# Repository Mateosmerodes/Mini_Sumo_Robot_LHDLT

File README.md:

# Mini_Sumo_Robot_LHDLT
Repositorio de información y código del proyecto mini-sumo del equipo LHDT (Los Hombres de las Tabernas).

- [`Robot_Mini-Sumo/`](Robot_Mini-Sumo/README.md): diseño actual (v2 básico, 2 motores, placa de agujero pasante).
- [`archivo/v1-4motores/`](archivo/v1-4motores/ARCHIVO.md): todo el diseño anterior (v1, 4 motores), guardado tal cual.

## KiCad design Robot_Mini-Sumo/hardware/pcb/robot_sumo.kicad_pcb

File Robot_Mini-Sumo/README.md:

# 🍺 Robot Mini-Sumo · LHDT (Los Hombres de las Tabernas)

Robot mini-sumo autónomo (10 × 10 cm, < 500 g) para **Tecnología Eléctrica**, Grado en Robótica (USC). Reglamento de referencia: OSHWDem Mini Sumo.

**Equipo:** Mateo Esmerodes Rodríguez · Paulo Bouza García · Mario Costoya Mera

## Diseño actual: v2 básico (23/11/2026)

Robot sencillo para cumplir: **2 motores N20**, **ESP32-S3-DevKitC-1**, **2 sensores de distancia VL53L0X**, **2 sensores de suelo QRE1113**, batería LiPo 2S y el **módulo de arranque ST4RT** del profesor. Placa propia de **agujero pasante**, con los módulos enchufados y todo rotulado en la serigrafía.

Nada está montado ni probado todavía.

| Qué | Dónde |
|---|---|
| Diseño completo: piezas, pines, placa, cálculos, montaje y compra | [docs/01-Diseno-v2-basico.md](docs/01-Diseno-v2-basico.md) |
| Proyecto KiCad (esquemático y PCB) | [hardware/pcb/](hardware/pcb/) |
| Ficheros para pedir la placa (Gerber, BOM, esquema en PDF) | [hardware/pcb/fabricacion/](hardware/pcb/fabricacion/) |
| Chasis (script de Fusion 360, STEP, STL e imágenes) | [hardware/chasis/](hardware/chasis/README.md) |
| Firmware (Arduino) | [firmware/sumo_lhdt_v2/](firmware/sumo_lhdt_v2/) |
| Cambios | [CHANGELOG.md](CHANGELOG.md) |

## Diseño anterior

Todo el trabajo anterior (v1: 4 motores, placa SMD, simulaciones, ficha técnica entregada…) está guardado tal cual en [`../archivo/v1-4motores/`](../archivo/v1-4motores/ARCHIVO.md) (el commit `7e4c077` tiene el estado completo antes de moverlo).

## Regenerar la placa (Linux, KiCad 7 o superior)

```bash
cd hardware/pcb/scripts
python3 gen_lib.py && python3 gen_pro.py && python3 gen_sch.py   # librería, proyecto y esquemático
python3 gen_pcb.py                                               # coloca componentes (BORRA el rutado)
python3 autoroute.py freerouting-1.9.0.jar 150                   # rutado con Freerouting 1.9 (Java)
python3 drc.py && python3 paridad.py                             # DRC y esquemático = placa
./fabricacion.sh                                                 # Gerber, BOM y PDF
```

`robot_sumo.kicad_pcb` ya está rutado: **no hace falta** ejecutar `gen_pcb.py` ni `autoroute.py` para pedir la placa (si se ejecutan, el rutado sale distinto y hay que revisarlo otra vez).

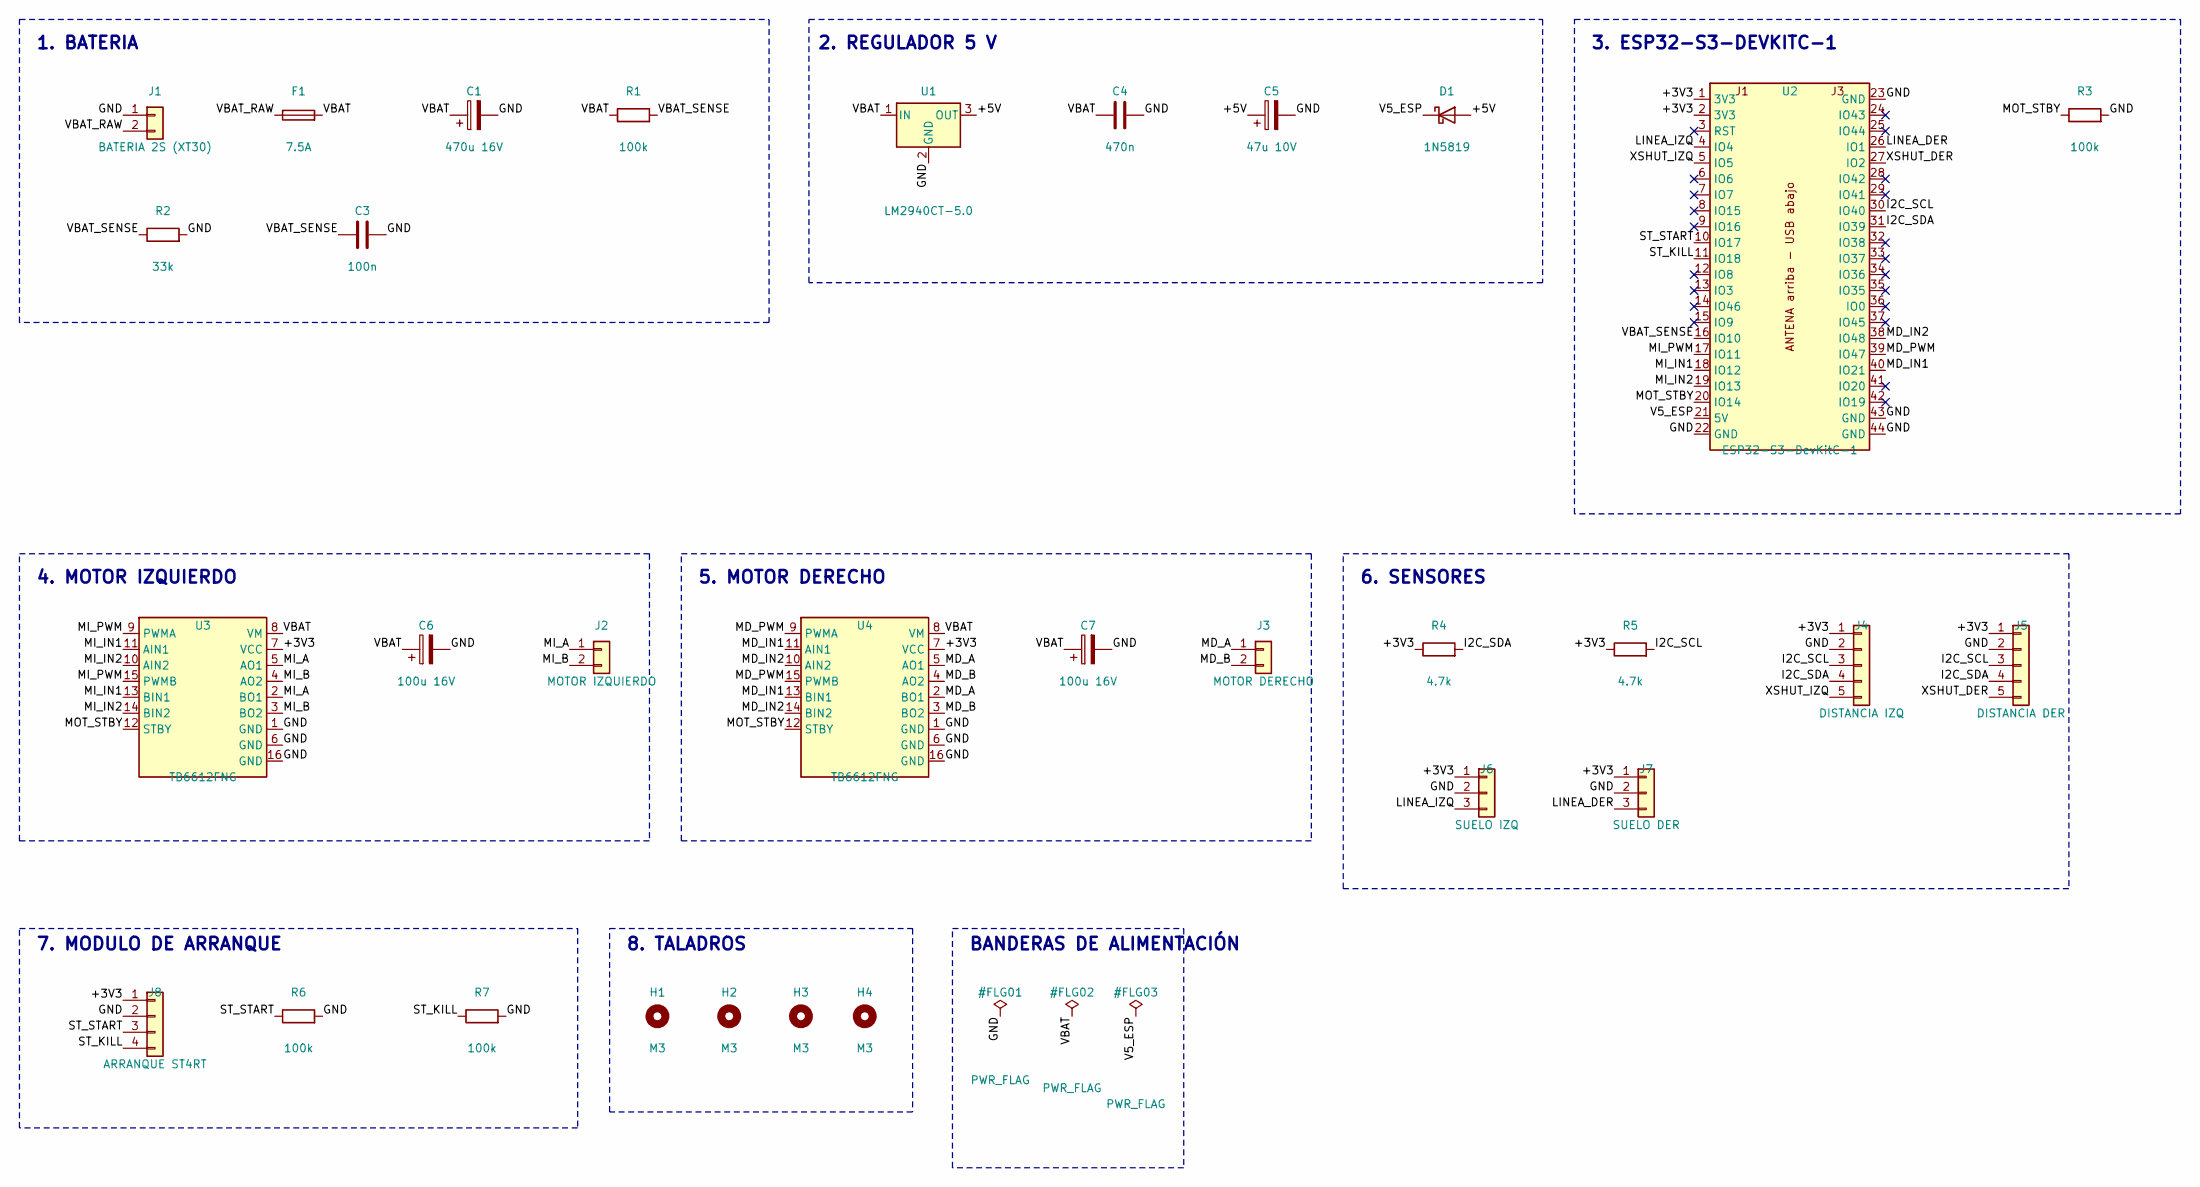
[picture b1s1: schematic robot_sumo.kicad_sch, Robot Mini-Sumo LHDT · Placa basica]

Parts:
C1: 470u 16V; CP_Radial_D8.0mm_P3.50mm; MPN Electrolítico 470 µF 16 V, Ø8 mm, paso 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
C3: 100n; C_Disc_D5.0mm_W2.5mm_P5.00mm; MPN Condensador cerámico de disco, paso 5 mm
C4: 470n; C_Disc_D5.0mm_W2.5mm_P5.00mm; MPN Condensador cerámico de disco, paso 5 mm
C5: 47u 10V; CP_Radial_D6.3mm_P2.50mm; MPN Electrolítico 47 µF 10 V, Ø6,3 mm, paso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
C6, C7: 100u 16V; CP_Radial_D6.3mm_P2.50mm; MPN Electrolítico 100 µF 16 V, Ø6,3 mm, pas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
D1: 1N5819; D_DO-41_SOD81_P10.16mm_Horizontal; MPN Diodo Schottky 1N5819 (DO-41)
F1: 7.5A; Fuseholder_Blade_Mini_Keystone_3568; MPN Portafusibles Keystone 3568 + fusible d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
H1, H2, H3, H4: M3; MountingHole_3.2mm_M3
J1: BATERIA 2S (XT30); AMASS_XT30UPB-M_1x02_P5.0mm_Vertical; MPN AMASS XT30UPB-M macho, vertical, de agu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
J2: MOTOR IZQUIERDO; TerminalBlock_Phoenix_MKDS-1,5-2-5.08_1x02_P5.08mm_Horizont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; MPN Clema de tornillo 2 polos, paso 5,08 mm
J3: MOTOR DERECHO; TerminalBlock_Phoenix_MKDS-1,5-2-5.08_1x02_P5.08mm_Horizont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; MPN Clema de tornillo 2 polos, paso 5,08 mm
J4: DISTANCIA IZQ; PinHeader_1x05_P2.54mm_Vertical; MPN Tira macho 1×5, 2,54 mm. Cable Dupont a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
J5: DISTANCIA DER; PinHeader_1x05_P2.54mm_Vertical; MPN Tira macho 1×5, 2,54 mm. Cable Dupont a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
J6: SUELO IZQ; PinHeader_1x03_P2.54mm_Vertical; MPN Tira macho 1×3, 2,54 mm. Cable Dupont a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
J7: SUELO DER; PinHeader_1x03_P2.54mm_Vertical; MPN Tira macho 1×3, 2,54 mm. Cable Dupont a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
J8: ARRANQUE ST4RT; PinHeader_1x04_P2.54mm_Vertical; MPN Tira macho 1×4, 2,54 mm. Cable Dupont a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
R1, R3, R6, R7: 100k; R_Axial_DIN0207_L6.3mm_D2.5mm_P10.16mm_Horizontal; MPN Resistencia 1/4 W
R2: 33k; R_Axial_DIN0207_L6.3mm_D2.5mm_P10.16mm_Horizontal; MPN Resistencia 1/4 W
R4, R5: 4.7k; R_Axial_DIN0207_L6.3mm_D2.5mm_P10.16mm_Horizontal; MPN Resistencia 1/4 W
U1: LM2940CT-5.0; TO-220-3_Vertical; MPN LM2940CT-5.0 (TO-220). Mismo patillaje 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
U2: ESP32-S3-DevKitC-1; ESP32-S3-DevKitC-1_Zocalo; MPN ESP32-S3-DevKitC-1 + 2 tiras hembra 1×2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
U3: TB6612FNG; TB6612FNG_Modulo; MPN Módulo TB6612FNG (SparkFun ROB-14450 o 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
U4: TB6612FNG; TB6612FNG_Modulo_Girado; MPN Módulo TB6612FNG (SparkFun ROB-14450 o 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

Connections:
+3V3: J4.1, J5.1, J6.1, J7.1, J8.1, R4.1, R5.1, U2.1 (3V3), U2.2 (3V3), U3.7 (VCC), U4.7 (VCC)
+5V: C5.1, D1.2 (A), U1.3 (OUT)
GND: C1.2, C3.2, C4.2, C5.2, C6.2, C7.2, J1.1, J4.2, J5.2, J6.2, J7.2, J8.2, R2.2, R3.2, R6.2, R7.2, U1.2 (GND), U2.22 (GND), U2.23 (GND), U2.43 (GND), U2.44 (GND), U3.1 (GND), U3.6 (GND), U3.16 (GND), U4.1 (GND), U4.6 (GND), U4.16 (GND)
I2C_SCL: J4.3, J5.3, R5.2, U2.30 (IO40)
I2C_SDA: J4.4, J5.4, R4.2, U2.31 (IO39)
LINEA_DER: J7.3, U2.26 (IO1)
LINEA_IZQ: J6.3, U2.4 (IO4)
MD_A: J3.1, U4.2 (BO1), U4.5 (AO1)
MD_B: J3.2, U4.3 (BO2), U4.4 (AO2)
MD_IN1: U2.40 (IO21), U4.11 (AIN1), U4.13 (BIN1)
MD_IN2: U2.38 (IO48), U4.10 (AIN2), U4.14 (BIN2)
MD_PWM: U2.39 (IO47), U4.9 (PWMA), U4.15 (PWMB)
MI_A: J2.1, U3.2 (BO1), U3.5 (AO1)
MI_B: J2.2, U3.3 (BO2), U3.4 (AO2)
MI_IN1: U2.18 (IO12), U3.11 (AIN1), U3.13 (BIN1)
MI_IN2: U2.19 (IO13), U3.10 (AIN2), U3.14 (BIN2)
MI_PWM: U2.17 (IO11), U3.9 (PWMA), U3.15 (PWMB)
MOT_STBY: R3.1, U2.20 (IO14), U3.12 (STBY), U4.12 (STBY)
ST_KILL: J8.4, R7.1, U2.11 (IO18)
ST_START: J8.3, R6.1, U2.10 (IO17)
V5_ESP: D1.1 (K), U2.21 (5V)
VBAT: C1.1, C4.1, C6.1, C7.1, F1.2, R1.1, U1.1 (IN), U3.8 (VM), U4.8 (VM)
VBAT_RAW: F1.1, J1.2
VBAT_SENSE: C3.1, R1.2, R2.1, U2.16 (IO10)
XSHUT_DER: J5.5, U2.27 (IO2)
XSHUT_IZQ: J4.5, U2.5 (IO5)

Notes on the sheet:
1. BATERIA
2. REGULADOR 5 V
3. ESP32-S3-DEVKITC-1
4. MOTOR IZQUIERDO
5. MOTOR DERECHO
6. SENSORES
7. MODULO DE ARRANQUE
8. TALADROS
BANDERAS DE ALIMENTACIÓN

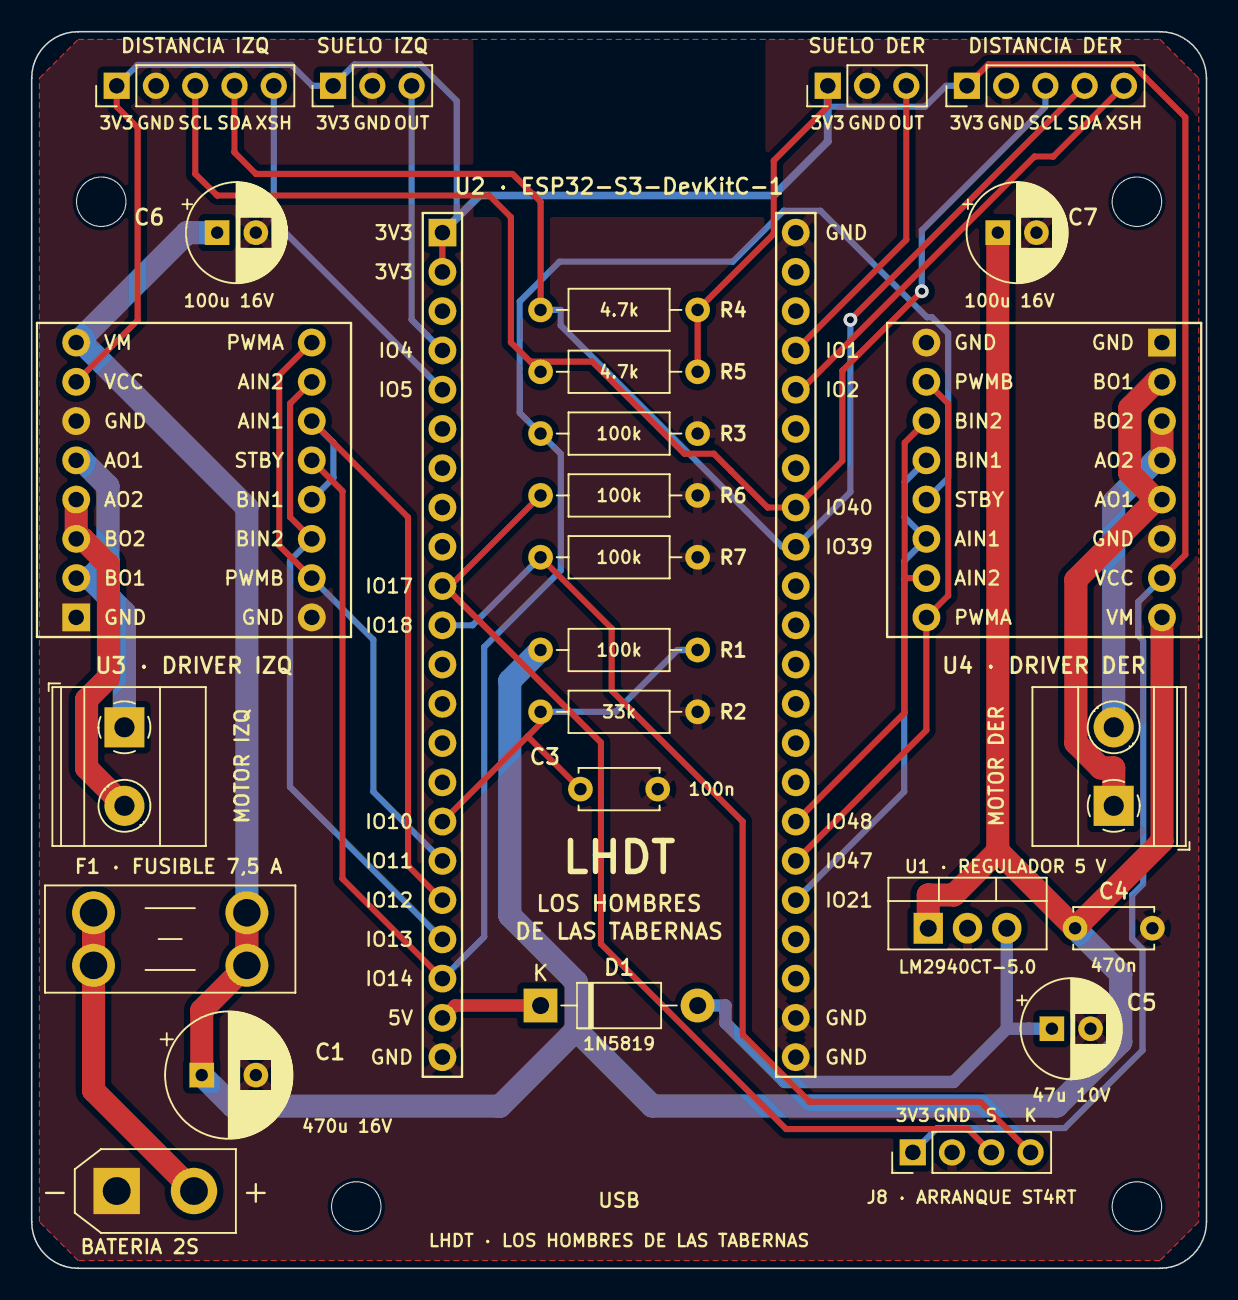
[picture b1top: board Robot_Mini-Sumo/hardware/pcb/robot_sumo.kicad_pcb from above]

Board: 2 copper layers, 76.0 x 80.0 mm, 31 parts (0 on the bottom side), 26 nets.

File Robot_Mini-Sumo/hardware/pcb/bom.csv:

Comment,Designator,Footprint,LCSC,MPN,Cantidad
470u 16V,C1,CP_Radial_D8.0mm_P3.50mm,,"Electrolítico 470 µF 16 V, Ø8 mm, paso 3,5 mm (reserva de los motores)",1
100n,C3,C_Disc_D5.0mm_W2.5mm_P5.00mm,,"Condensador cerámico de disco, paso 5 mm",1
470n,C4,C_Disc_D5.0mm_W2.5mm_P5.00mm,,"Condensador cerámico de disco, paso 5 mm",1
47u 10V,C5,CP_Radial_D6.3mm_P2.50mm,,"Electrolítico 47 µF 10 V, Ø6,3 mm, paso 2,5 mm",1
100u 16V,"C6,C7",CP_Radial_D6.3mm_P2.50mm,,"Electrolítico 100 µF 16 V, Ø6,3 mm, paso 2,5 mm",2
1N5819,D1,D_DO-41_SOD81_P10.16mm_Horizontal,,Diodo Schottky 1N5819 (DO-41),1
7.5A,F1,Fuseholder_Blade_Mini_Keystone_3568,,"Portafusibles Keystone 3568 + fusible de cuchilla mini (ATM) de 7,5 A",1
BATERIA 2S (XT30),J1,AMASS_XT30UPB-M_1x02_P5.0mm_Vertical,,"AMASS XT30UPB-M macho, vertical, de agujero pasante",1
MOTOR IZQUIERDO,J2,"TerminalBlock_Phoenix_MKDS-1,5-2-5.08_1x02_P5.08mm_Horizontal",,"Clema de tornillo 2 polos, paso 5,08 mm",1
MOTOR DERECHO,J3,"TerminalBlock_Phoenix_MKDS-1,5-2-5.08_1x02_P5.08mm_Horizontal",,"Clema de tornillo 2 polos, paso 5,08 mm",1
DISTANCIA IZQ,J4,PinHeader_1x05_P2.54mm_Vertical,,"Tira macho 1×5, 2,54 mm. Cable Dupont al módulo VL53L0X",1
DISTANCIA DER,J5,PinHeader_1x05_P2.54mm_Vertical,,"Tira macho 1×5, 2,54 mm. Cable Dupont al módulo VL53L0X",1
SUELO IZQ,J6,PinHeader_1x03_P2.54mm_Vertical,,"Tira macho 1×3, 2,54 mm. Cable Dupont al módulo QRE1113 analógico",1
SUELO DER,J7,PinHeader_1x03_P2.54mm_Vertical,,"Tira macho 1×3, 2,54 mm. Cable Dupont al módulo QRE1113 analógico",1
ARRANQUE ST4RT,J8,PinHeader_1x04_P2.54mm_Vertical,,"Tira macho 1×4, 2,54 mm. Cable Dupont a medida hasta el módulo",1
100k,"R1,R3,R6,R7",R_Axial_DIN0207_L6.3mm_D2.5mm_P10.16mm_Horizontal,,Resistencia 1/4 W,4
33k,R2,R_Axial_DIN0207_L6.3mm_D2.5mm_P10.16mm_Horizontal,,Resistencia 1/4 W,1
4.7k,"R4,R5",R_Axial_DIN0207_L6.3mm_D2.5mm_P10.16mm_Horizontal,,Resistencia 1/4 W,2
LM2940CT-5.0,U1,TO-220-3_Vertical,,LM2940CT-5.0 (TO-220). Mismo patillaje que un 7805,1
ESP32-S3-DevKitC-1,U2,ESP32-S3-DevKitC-1_Zocalo,,"ESP32-S3-DevKitC-1 + 2 tiras hembra 1×22 de 2,54 mm",1
TB6612FNG,U3,TB6612FNG_Modulo,,Módulo TB6612FNG (SparkFun ROB-14450 o clon con el mismo patillaje) + 2 tiras hembra 1×8,1
TB6612FNG,U4,TB6612FNG_Modulo_Girado,,Módulo TB6612FNG (SparkFun ROB-14450 o clon con el mismo patillaje) + 2 tiras hembra 1×8,1

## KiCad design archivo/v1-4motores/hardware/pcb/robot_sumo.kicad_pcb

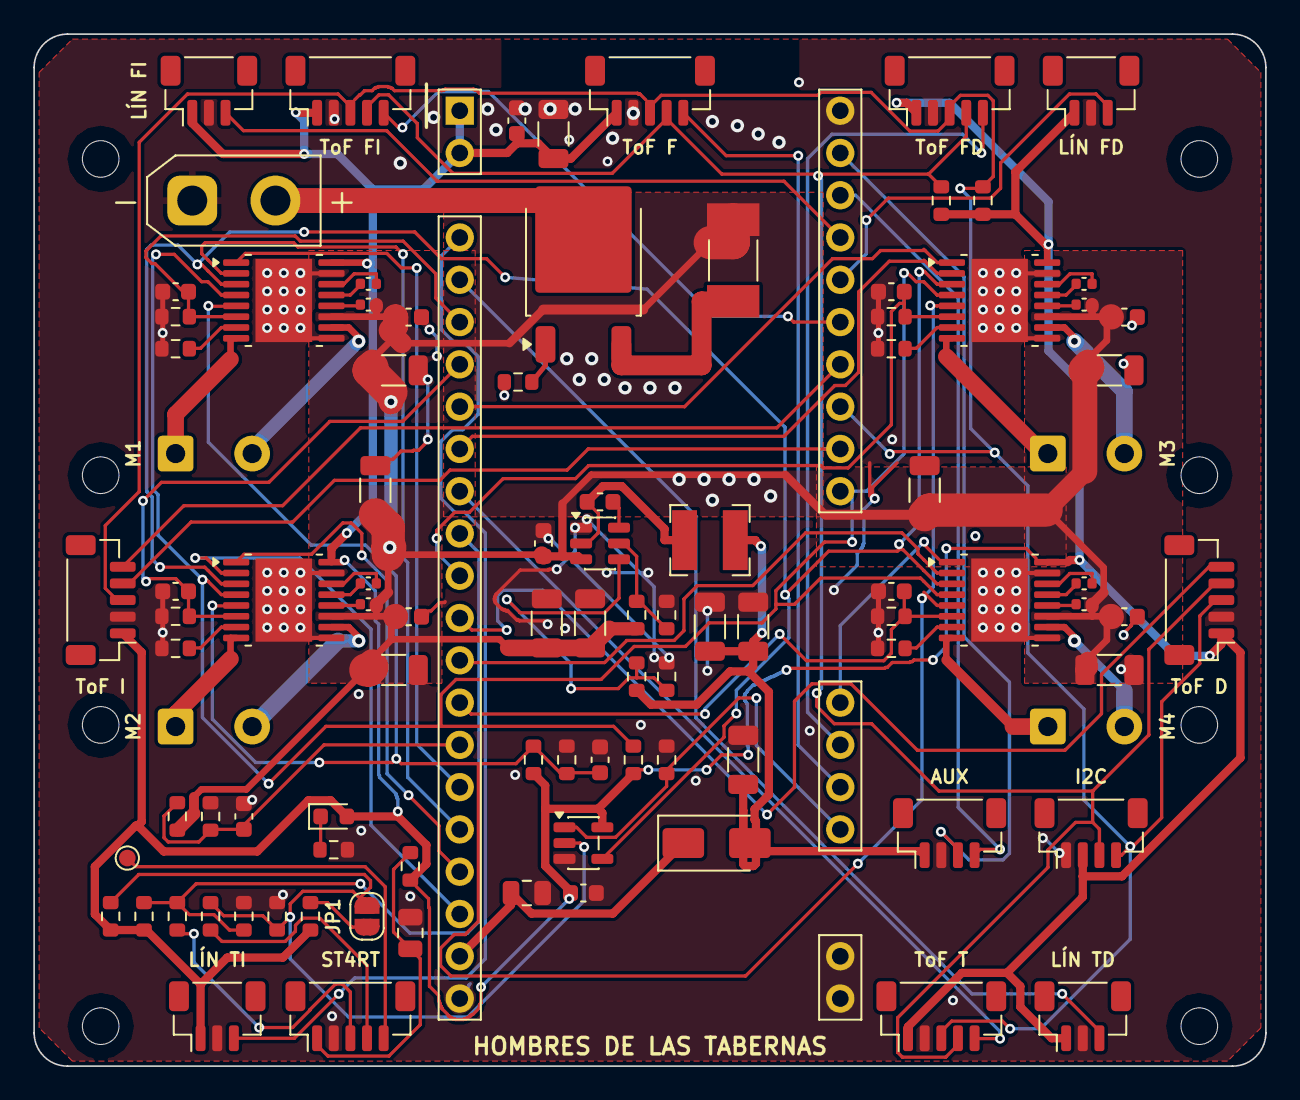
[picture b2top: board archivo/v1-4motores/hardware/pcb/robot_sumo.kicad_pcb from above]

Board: 2 copper layers, 74.0 x 62.0 mm, 106 parts (0 on the bottom side), 75 nets.

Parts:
C1, C2: 22u 25V; C_1206_3216Metric
C3, C6, C7, C14, C15, C17: 100n; C_0603_1608Metric
C4, C5, C24, C34, C44, C54: 10u 25V; C_1206_3216Metric
C8, C9, C10, C13: 22u 10V; C_1206_3216Metric
C11, C62: 10u 10V; C_0805_2012Metric
C20, C30, C40, C50: 10n; C_0603_1608Metric
C21, C31, C41, C51: 100n 16V; C_0402_1005Metric
C22, C32, C42, C52: 22n 50V; C_0402_1005Metric
C23, C33, C43, C53: 100n 50V; C_0603_1608Metric
D1: SS34; D_SMA
D3: verde; LED_0603_1608Metric
F1: 15A; Fuse_Littelfuse-NANO2-451_453
H1, H2, H3, H4, H5, H6, H7, H8: M2; MountingHole_2.2mm_M2
J1: XT30 BATERÍA 2S; AMASS_XT30UPB-M_1x02_P5.0mm_Vertical
J3: MOTOR 1; SolderWire-0.5sqmm_1x02_P4.6mm_D0.9mm_OD2.1mm
J4: MOTOR 2; SolderWire-0.5sqmm_1x02_P4.6mm_D0.9mm_OD2.1mm
J5: MOTOR 3; SolderWire-0.5sqmm_1x02_P4.6mm_D0.9mm_OD2.1mm
J6: MOTOR 4; SolderWire-0.5sqmm_1x02_P4.6mm_D0.9mm_OD2.1mm
J7: ToF IZQ; JST_SH_BM05B-SRSS-TB_1x05-1MP_P1.00mm_Vertical
J8: ToF FRONT-IZQ; JST_SH_BM05B-SRSS-TB_1x05-1MP_P1.00mm_Vertical
J9: ToF FRONTAL; JST_SH_BM05B-SRSS-TB_1x05-1MP_P1.00mm_Vertical
J10: ToF FRONT-DER; JST_SH_BM05B-SRSS-TB_1x05-1MP_P1.00mm_Vertical
J11: ToF DER; JST_SH_BM05B-SRSS-TB_1x05-1MP_P1.00mm_Vertical
J12: ToF TRASERO; JST_SH_BM05B-SRSS-TB_1x05-1MP_P1.00mm_Vertical
J13: LÍNEA FRONT-IZQ; JST_SH_BM03B-SRSS-TB_1x03-1MP_P1.00mm_Vertical
J14: LÍNEA FRONT-DER; JST_SH_BM03B-SRSS-TB_1x03-1MP_P1.00mm_Vertical
J15: LÍNEA TRAS-IZQ; JST_SH_BM03B-SRSS-TB_1x03-1MP_P1.00mm_Vertical
J16: LÍNEA TRAS-DER; JST_SH_BM03B-SRSS-TB_1x03-1MP_P1.00mm_Vertical
J17: ST4RT (módulo IR); JST_SH_BM05B-SRSS-TB_1x05-1MP_P1.00mm_Vertical
J18: I2C (QWIIC); JST_SH_BM04B-SRSS-TB_1x04-1MP_P1.00mm_Vertical
J19: AUX (UART/servo); JST_SH_BM04B-SRSS-TB_1x04-1MP_P1.00mm_Vertical
JP1: BANCO SIN MÓDULO; SolderJumper-2_P1.3mm_Open_RoundedPad1.0x1.5mm
L1: 3.3u; L_Bourns-SRN4018
Q1: AOD4185; TO-252-2
R1, R8, R14, R15, R16, R67, R68, R69: 10k; R_0603_1608Metric
R3, R5, R17, R65, R66: 100k; R_0603_1608Metric
R4: 33k; R_0603_1608Metric
R6: 51k; R_0603_1608Metric
R7: 59k; R_0603_1608Metric
R9, R63, R64: 1k; R_0603_1608Metric
R20, R30, R40, R50: 1.5k; R_0603_1608Metric
R21, R31, R41, R51: 20k; R_0603_1608Metric
R60, R61: 4.7k; R_0603_1608Metric
R62: 10; R_0603_1608Metric
TP1: IR_RAW; TestPoint_Pad_D1.0mm
U1: ESP32-S3-DevKitC-1; ESP32-S3-DevKitC-1_Zocalo
U2: TPS563201; SOT-23-6
U3: 74LVC1G08; SOT-23-5
U5, U6, U7, U8: DRV8874; HTSSOP-16-1EP_4.4x5mm_P0.65mm_EP3.4x5mm_Mask2.46x2.31mm

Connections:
+3V3: C13.1, C14.1, C15.1, D3.2, J7.1, J8.1, J9.1, J10.1, J11.1, J12.1, J13.1, J14.1, J15.1, J16.1, J18.2, R14.1, R16.1, R60.1, R61.1, R62.1, R67.1, R68.1, R69.1, U1.1, U1.2, U3.5, U5.16, U6.16, U7.16, U8.16
+5V: C8.1, C9.1, C10.1, D1.2, J19.1, L1.2, R7.1
AUX_RX: J19.4, U1.25
AUX_TX: J19.3, U1.24
BUCK_BST: C7.2, U2.6
BUCK_EN: R5.2, R6.1, U2.5
BUCK_FB: R7.2, R8.1, U2.4
BUCK_SW: C7.1, L1.1, U2.2
DRV_EN: R17.1, U1.40, U3.1
DRV_VREF: C17.1, R14.2, R15.1, U5.5, U6.5, U7.5, U8.5
DRV_nFAULT: R16.2, U1.32, U5.4, U6.4, U7.4, U8.4
DRV_nSLEEP: U3.4, U5.3, U6.3, U7.3, U8.3
GND: C1.2, C2.2, C3.2, C4.2, C5.2, C6.2, C8.2, C9.2, C10.2, C11.2, C13.2, C14.2, C15.2, C17.2, C20.2, C23.2, C24.2, C30.2, C33.2, C34.2, C40.2, C43.2, C44.2, C50.2, C53.2, C54.2, C62.2, J1.1, J7.2, J8.2, J9.2, J10.2, J11.2, J12.2, J13.2, J14.2, J15.2, J16.2, J17.2, J18.1, J19.2, R1.2, R4.2, R6.2, R8.2, R9.2, R15.2, R17.2, R20.2, R21.2, R30.2, R31.2, R40.2, R41.2, R50.2, R51.2, R65.2, R66.2, U1.22, U1.23, U1.43, U1.44, U2.1, U3.3, U5.9, U5.15, U5.17, U6.9, U6.15, U6.17, U7.9, U7.15, U7.17, U8.9, U8.15, U8.17
I2C_SCL: J7.3, J8.3, J9.3, J10.3, J11.3, J12.3, J18.4, R61.2, U1.30
I2C_SDA: J7.4, J8.4, J9.4, J10.4, J11.4, J12.4, J18.3, R60.2, U1.31
IR_START: R63.2, R65.1, R68.2, U1.11
ISENSE_M1: C20.1, R20.1, U1.6, U5.6
ISENSE_M2: C30.1, R30.1, U1.7, U6.6
ISENSE_M3: C40.1, R40.1, U1.12, U7.6
ISENSE_M4: C50.1, R50.1, U1.15, U8.6
JP1_A: JP1.1, R67.2
LED_PWR_K: D3.1, R9.1
LINE_FL: J13.3, U1.26
LINE_FR: J14.3, U1.27
LINE_RL: J15.3, U1.4
LINE_RR: J16.3, U1.5
M1_CPH: C22.1, U5.13
M1_CPL: C22.2, U5.14
M1_IMODE: R21.1, U5.7
M1_IN1: U1.17, U5.1
M1_IN2: U1.18, U5.2
M1_OUTA: J3.1, U5.8
M1_OUTB: J3.2, U5.10
M1_VCP: C21.1, U5.12
M2_CPH: C32.1, U6.13
M2_CPL: C32.2, U6.14
M2_IMODE: R31.1, U6.7
M2_IN1: U1.19, U6.1
M2_IN2: U1.20, U6.2
M2_OUTA: J4.1, U6.8
M2_OUTB: J4.2, U6.10
M2_VCP: C31.1, U6.12
M3_CPH: C42.1, U7.13
M3_CPL: C42.2, U7.14
M3_IMODE: R41.1, U7.7
M3_IN1: U1.8, U7.1
M3_IN2: U1.9, U7.2
M3_OUTA: J5.1, U7.8
M3_OUTB: J5.2, U7.10
M3_VCP: C41.1, U7.12
M4_CPH: C52.1, U8.13
M4_CPL: C52.2, U8.14
M4_IMODE: R51.1, U8.7
M4_IN1: U1.37, U8.1
M4_IN2: U1.14, U8.2
M4_OUTA: J6.1, U8.8
M4_OUTB: J6.2, U8.10
M4_VCP: C51.1, U8.12
Q1_G: Q1.1, R1.1
ST_IR_RAW: J17.5, TP1.1
ST_KILL: JP1.2, R64.2, R66.1, R69.2, U3.2
ST_KILL_IN: J17.4, R64.1
ST_START_IN: J17.3, R63.1
ST_VCC: C62.1, J17.1, R62.2
V5_ESP: C11.1, D1.1, U1.21
VBAT: C1.1, C2.1, C4.1, C5.1, C6.1, C21.2, C23.1, C24.1, C31.2, C33.1, C34.1, C41.2, C43.1, C44.1, C51.2, C53.1, C54.1, F1.2, R3.1, R5.1, U2.3, U5.11, U6.11, U7.11, U8.11
VBAT_RAW: J1.2, Q1.2
VBAT_REV: F1.1, Q1.3
VBAT_SENSE: C3.1, R3.2, R4.1, U1.16
XSHUT_B: J12.5, U1.10
XSHUT_F: J9.5, U1.39
XSHUT_FL: J8.5, U1.28
XSHUT_FR: J10.5, U1.38
XSHUT_L: J7.5, U1.29
XSHUT_R: J11.5, U1.13

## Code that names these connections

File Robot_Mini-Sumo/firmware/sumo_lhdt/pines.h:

// pines.h — ESP32-S3-DevKitC-1 sobre la placa base v1.2 (HOMBRES DE LAS TABERNAS)
// Fuente única: hardware/pcb/scripts/design.py. Si cambia allí, cambia aquí.
#pragma once

namespace pin {
// Sensores de línea QRE1113 (ADC1)
constexpr int LINE_FL = 1, LINE_FR = 2, LINE_RL = 4, LINE_RR = 5;
// IPROPI de los DRV8874 (ADC1): V = I · 455 µA/A · 1,5 kΩ
constexpr int ISENSE_M1 = 6, ISENSE_M2 = 7, ISENSE_M3 = 8, ISENSE_M4 = 9;
// Batería: divisor 100 k / 33 k (ADC1)
constexpr int VBAT_SENSE = 10;
// Motores (modo PWM del DRV8874). M1 izq. del., M2 izq. tras., M3 der. del., M4 der. tras.
constexpr int M1_IN1 = 11, M1_IN2 = 12, M2_IN1 = 13, M2_IN2 = 14;
constexpr int M3_IN1 = 15, M3_IN2 = 16, M4_IN1 = 45, M4_IN2 = 46;  // 45/46: pines de arranque, a 0 al encender
// DRV_EN: el firmware habilita los drivers. En la v1.2 nSLEEP = DRV_EN AND KILL (U3), así que el
// módulo de arranque puede dormirlos aunque este pin esté a 1.
constexpr int DRV_EN = 21, DRV_nFAULT = 38;
// I2C de los VL53L0X y XSHUT de cada uno
constexpr int I2C_SDA = 39, I2C_SCL = 40;
constexpr int XSHUT_L = 41, XSHUT_FL = 42, XSHUT_F = 47, XSHUT_FR = 48, XSHUT_R = 3, XSHUT_B = 17;
// Módulo de arranque ST4RT: salida S (START) a través de R63 (1 k), con R65 (100 k) a GND
constexpr int ST_START = 18;
// Botón BOOT de la DevKit (en la propia DevKit; GPIO0 no tiene zócalo en la placa base)
constexpr int BTN_USER = 0;
}  // namespace pin

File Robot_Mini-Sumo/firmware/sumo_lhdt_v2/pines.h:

// pines.h — ESP32-S3-DevKitC-1 sobre la placa v2 básica (LHDT · Los Hombres de las Tabernas)
// Fuente única: hardware/pcb/scripts/design.py (diccionario GPIO). Si cambia allí, cambia aquí.
#pragma once

namespace pin {
// Motor izquierdo (módulo TB6612FNG U3, canales A y B en paralelo)
constexpr int MI_PWM = 11, MI_IN1 = 12, MI_IN2 = 13;
// Motor derecho (módulo TB6612FNG U4, canales A y B en paralelo)
constexpr int MD_PWM = 47, MD_IN1 = 21, MD_IN2 = 48;
// STBY de los dos módulos: 0 = motores apagados (R3 lo deja a 0 mientras arranca la ESP32)
constexpr int MOT_STBY = 14;
// Sensores de suelo QRE1113 analógicos (ADC1)
constexpr int LINEA_IZQ = 4, LINEA_DER = 1;
// Sensores de distancia VL53L0X (I2C) y su pin XSHUT
constexpr int I2C_SDA = 39, I2C_SCL = 40;
constexpr int XSHUT_IZQ = 5, XSHUT_DER = 2;
// Módulo de arranque ST4RT: S (START) y K (KILL), con pull-down de 100 k en la placa
constexpr int ST_START = 17, ST_KILL = 18;
// Batería: divisor 100 k / 33 k (ADC1)
constexpr int VBAT_SENSE = 10;
}  // namespace pin

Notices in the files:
Robot_Mini-Sumo/hardware/pcb/robot_sumo.kicad_sch:
Licencia CERN-OHL-S v2
